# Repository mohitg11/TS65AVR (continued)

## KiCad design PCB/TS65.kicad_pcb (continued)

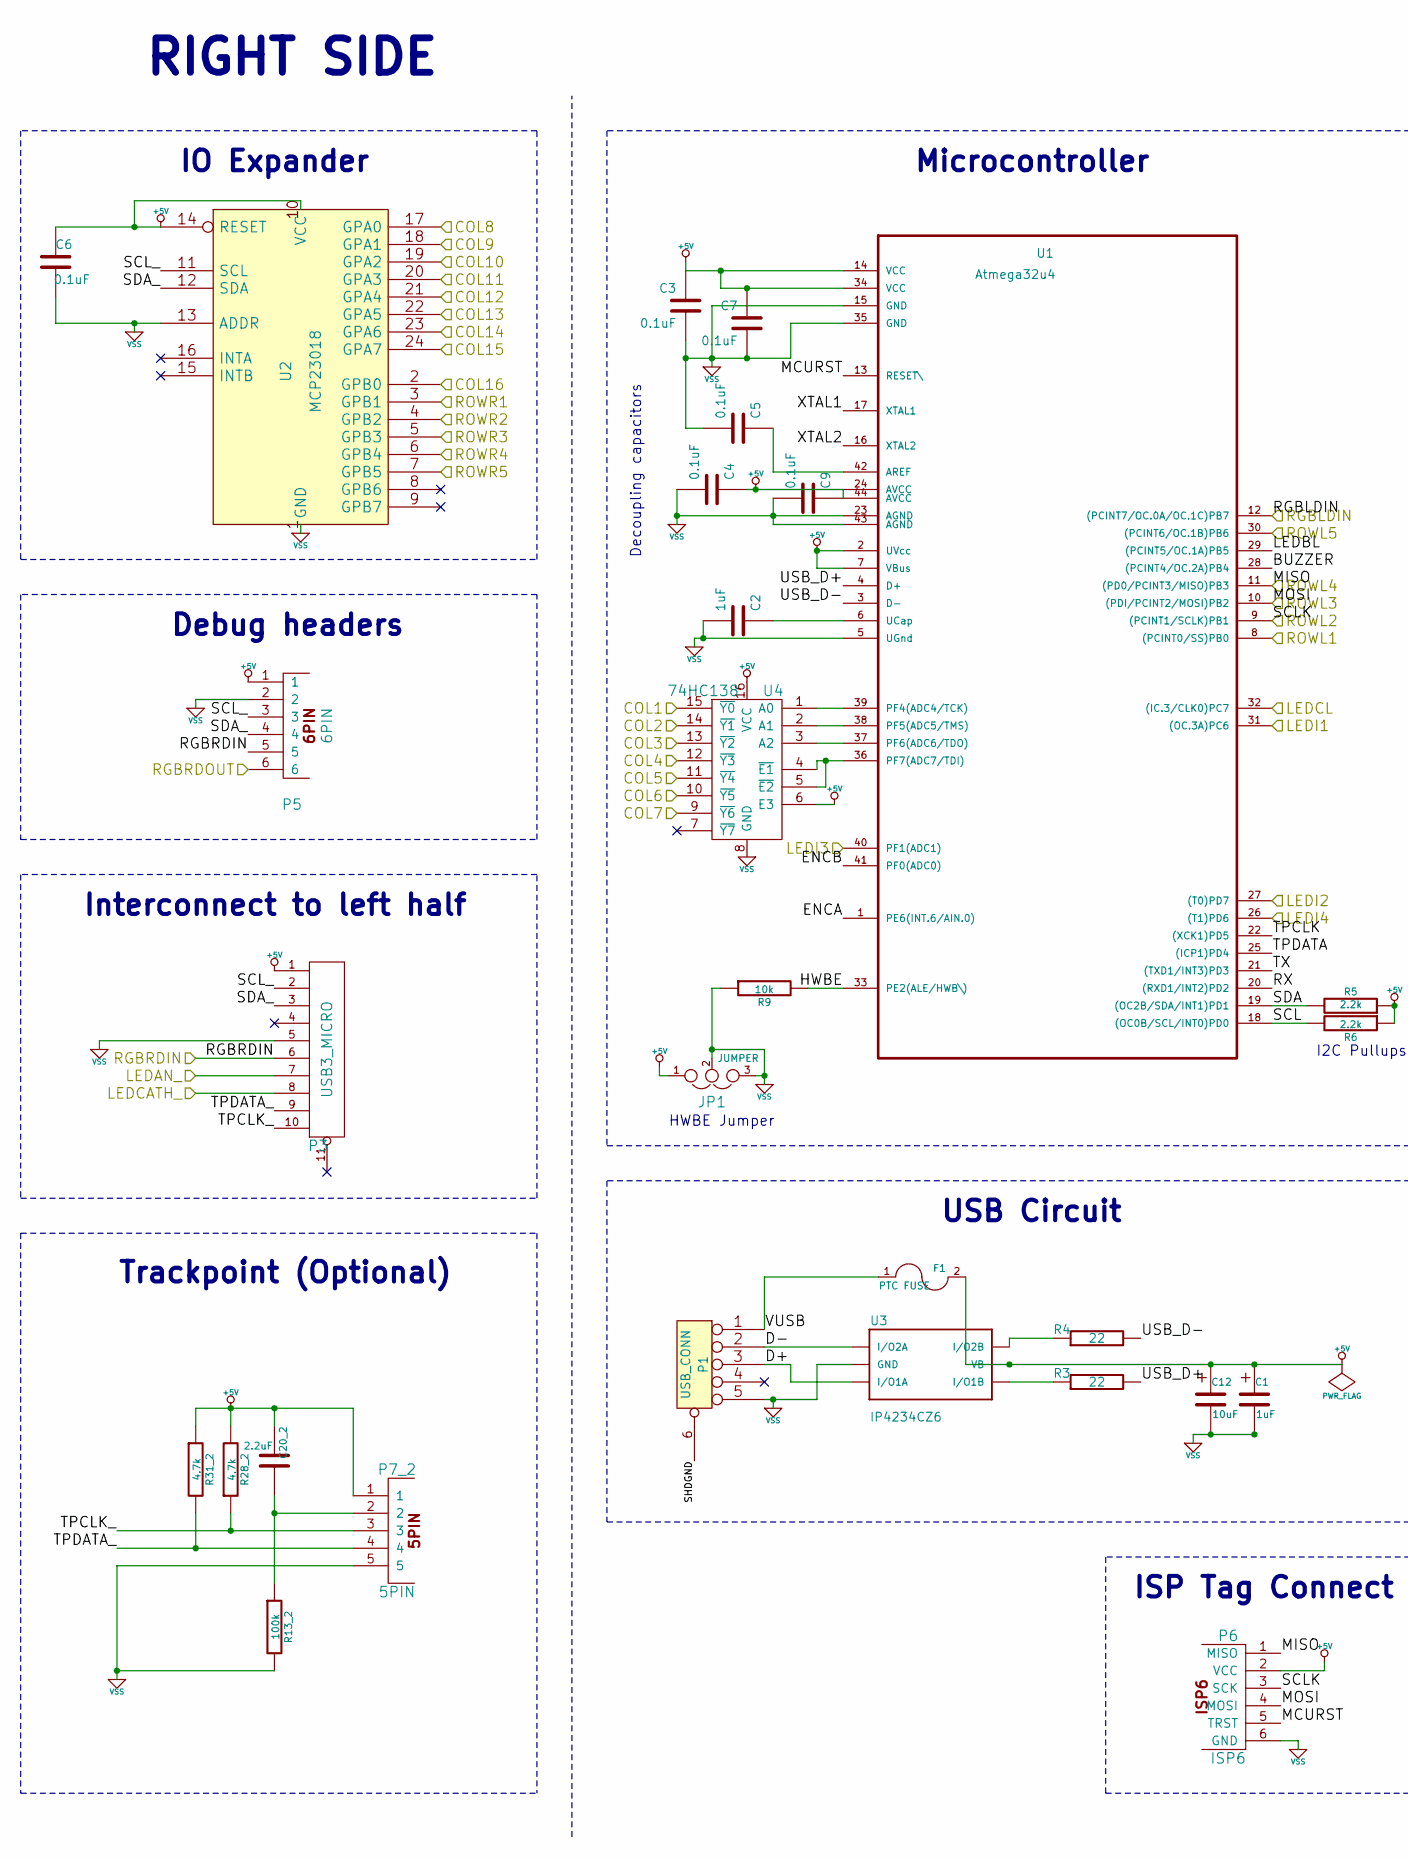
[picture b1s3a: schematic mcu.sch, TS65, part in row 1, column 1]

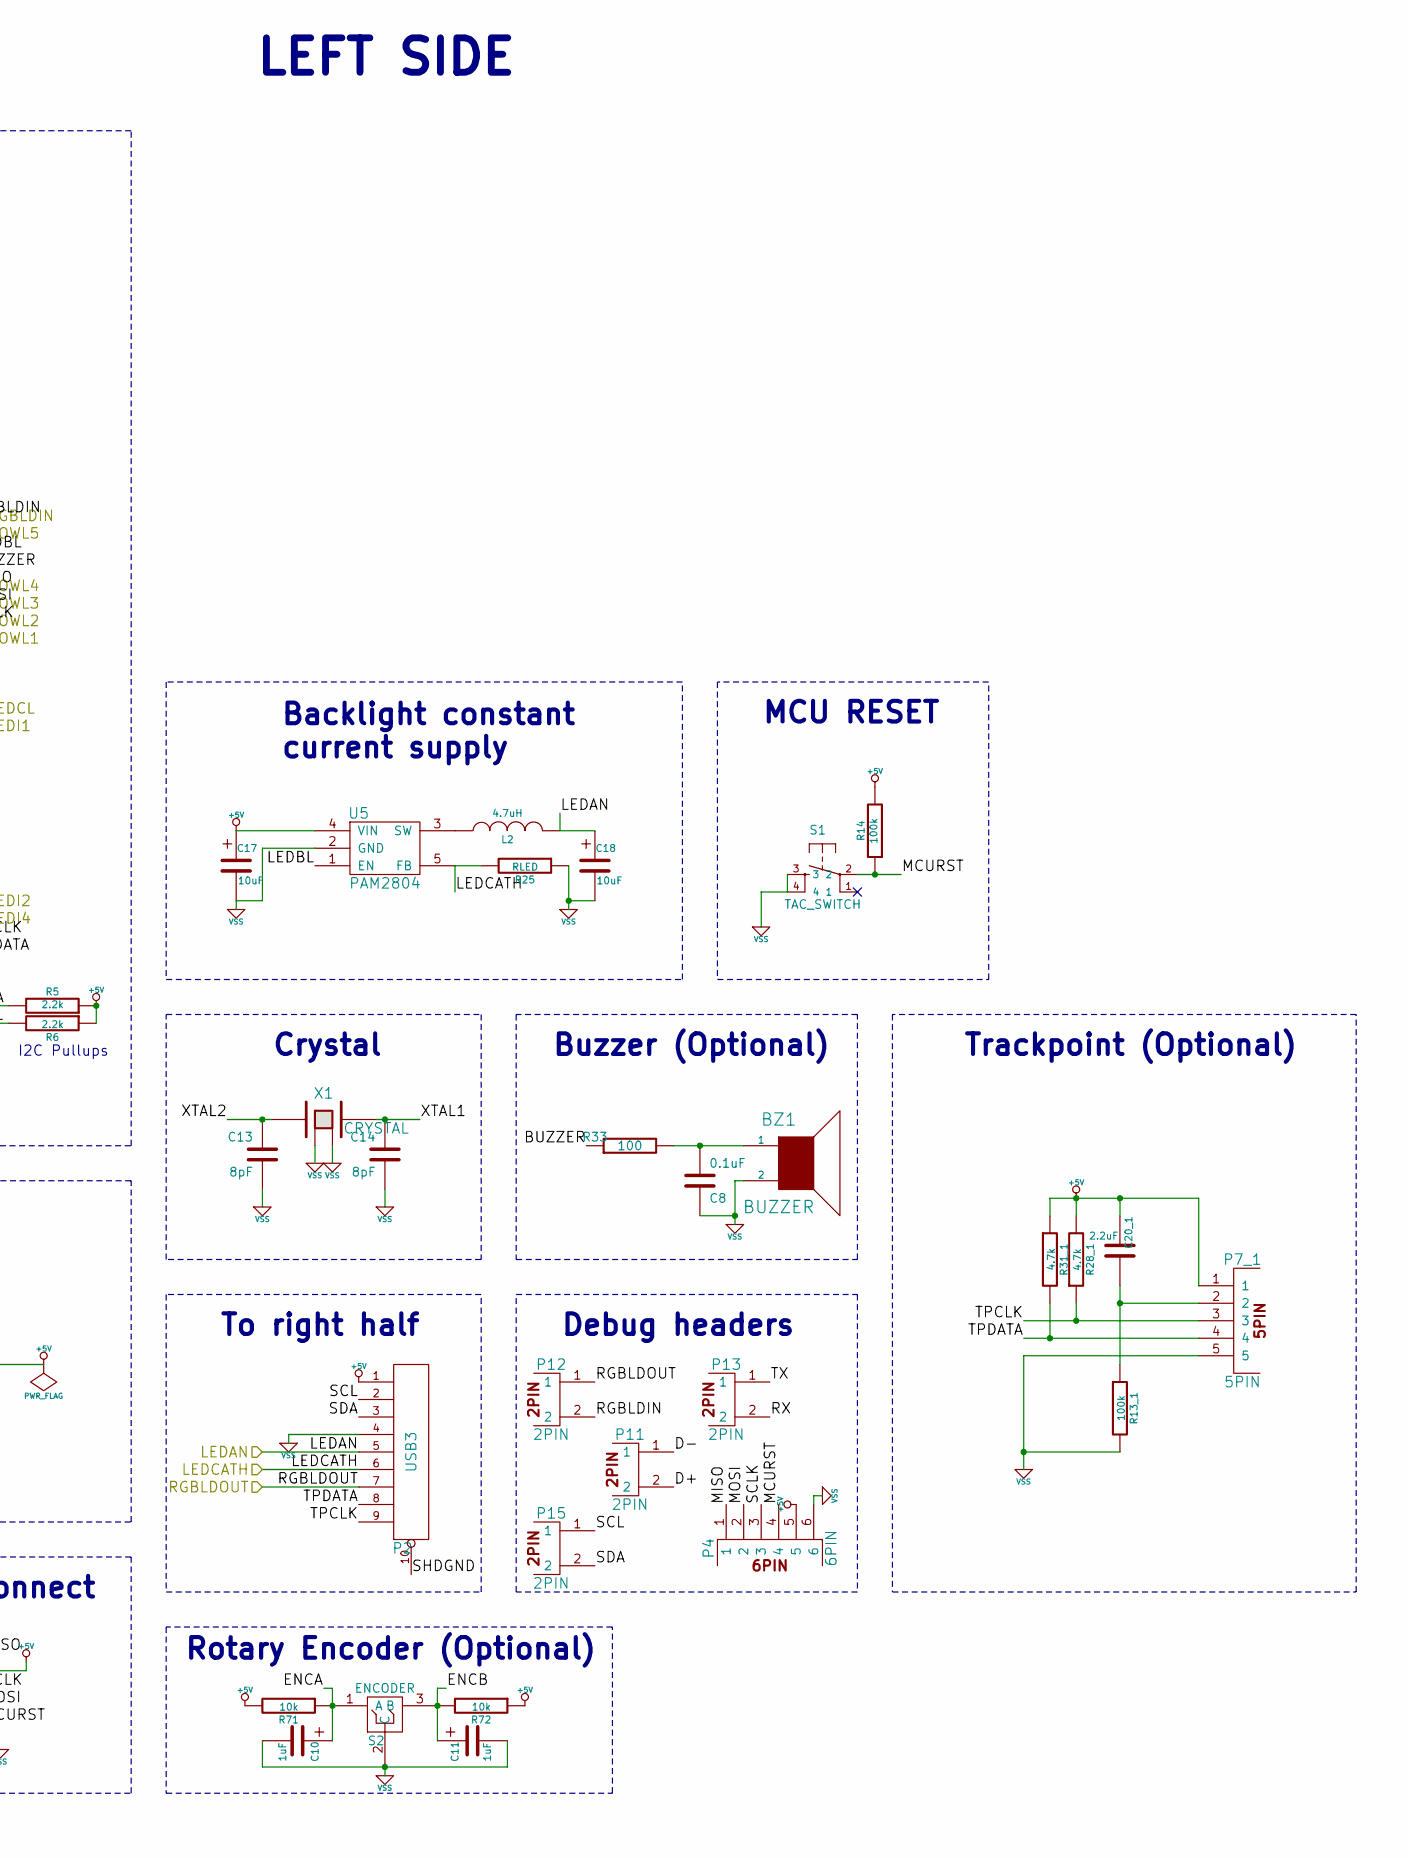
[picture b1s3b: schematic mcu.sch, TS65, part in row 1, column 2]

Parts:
BZ1: BUZZER; BUZZER_SMT
C1, C2, C10, C11: 1uF; SMD_0805
C3, C4, C5, C6, C7, C8, C9: 0.1uF; SMD_0805
C12, C17, C18: 10uF; SMD_0805
C13, C14: 8pF; SMD_0805
C20_1, C20_2: 2.2uF; SMD_0805
F1: PTC FUSE; Fuse_SMD1206
JP1: JUMPER; JUMPER_SMD_3
L2: 4.7uH; Inductor_Bourn_4mmx4mm
P1: USB_CONN; USB_Micro-B
P2: USB3; USB3_AFEMALE_MOD
P3: USB3_MICRO; USB3_MICROB
P4, P5: 6PIN; Pin_Header_1x06
P6: ISP6; TC2030_BIG
P7_1, P7_2: 5PIN; Pin_Header_1x05
P11, P12, P13, P15: 2PIN; Pin_Header_1x02
R3, R4: 22; SMD_0805
R5, R6: 2.2k; SMD_0805
R9, R71, R72: 10k; SMD_0805
R13_1, R13_2, R14: 100k; SMD_0805
R25: RLED; SMD_0805
R28_1, R28_2, R31_1, R31_2: 4.7k; SMD_0805
R33: 100; SMD_0805
S1: TAC_SWITCH; TACT_5.2x5.2
S2: ENCODER; ENCODER_12MM
U1: Atmega32u4; TQFP44
U2: MCP23018; SSOP-24
U3: IP4234CZ6; SOT457
U4: 74HC138; SO-16-N
U5: PAM2804; SOT-23-5
X1: CRYSTAL; NX3225SA

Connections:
+5V: C1.1, C3.1, C4.1, C6.1, C7.1, C9.1, C12.1, C17.1, C20_1.2, C20_2.2, F1.2, JP1.1, P2.1, P3.1, P4.5, P5.1, P6.2 (VCC), P7_1.1, P7_2.1, R5.1, R6.1, R14.2, R28_1.2, R28_2.2, R31_1.1, R31_2.1, R71.2, R72.1, U1.2 (UVcc), U1.7 (VBus), U1.14 (VCC), U1.24 (AVCC), U1.34 (VCC), U1.44 (AVCC), U2.10 (VCC), U2.14 (RESET), U3.5 (VB), U4.6 (E3), U4.16 (VCC), U5.4 (VIN); also elsewhere on the board
/Col1: U4.15 (~Y0); also elsewhere on the board
/Col2: U4.14 (~Y1); also elsewhere on the board
/Col3: U4.13 (~Y2); also elsewhere on the board
/Col4: U4.12 (~Y3); also elsewhere on the board
/Col5: U4.11 (~Y4); also elsewhere on the board
/Col6: U4.10 (~Y5); also elsewhere on the board
/Col7: U4.9 (~Y6); also elsewhere on the board
/Col8: U2.17 (GPA0); also elsewhere on the board
/Col9: U2.18 (GPA1); also elsewhere on the board
/Col10: U2.19 (GPA2); also elsewhere on the board
/Col11: U2.20 (GPA3); also elsewhere on the board
/Col12: U2.21 (GPA4); also elsewhere on the board
/Col13: U2.22 (GPA5); also elsewhere on the board
/Col14: U2.23 (GPA6); also elsewhere on the board
/Col15: U2.24 (GPA7); also elsewhere on the board
/Col16: U2.2 (GPB0); also elsewhere on the board
/RowL1: U1.8 ((PCINT0/SS)PB0); also elsewhere on the board
/RowL2: P4.3, P6.3 (SCK), U1.9 ((PCINT1/SCLK)PB1); also elsewhere on the board
/RowL3: P4.2, P6.4 (MOSI), U1.10 ((PDI/PCINT2/MOSI)PB2); also elsewhere on the board
/RowL4: P4.1, P6.1 (MISO), U1.11 ((PD0/PCINT3/MISO)PB3); also elsewhere on the board
/RowL5: U1.30 ((PCINT6/OC.1B)PB6); also elsewhere on the board
/RowR1: U2.3 (GPB1); also elsewhere on the board
/RowR2: U2.4 (GPB2); also elsewhere on the board
/RowR3: U2.5 (GPB3); also elsewhere on the board
/RowR4: U2.6 (GPB4); also elsewhere on the board
/RowR5: U2.7 (GPB5); also elsewhere on the board
/ledmatrix/LEDAN_: P3.7; also elsewhere on the board
/ledmatrix/LEDCATH_: P3.8; also elsewhere on the board
/ledmatrix/LEDCL: U1.32 ((IC.3/CLK0)PC7); also elsewhere on the board
/ledmatrix/LEDI1: U1.31 ((OC.3A)PC6); also elsewhere on the board
/ledmatrix/LEDI2: U1.27 ((T0)PD7); also elsewhere on the board
/ledmatrix/LEDI3: U1.40 (PF1(ADC1)); also elsewhere on the board
/ledmatrix/LEDI4: U1.26 ((T1)PD6); also elsewhere on the board
/ledmatrix/RGBLDIN: P12.2, U1.12 ((PCINT7/OC.0A/OC.1C)PB7); also elsewhere on the board
/ledmatrix/RGBRDIN: P3.6, P5.5; also elsewhere on the board
/ledmatrix/RGBRDOUT: P5.6; also elsewhere on the board
/mcu/BUZZER: R33.1, U1.28 ((PCINT4/OC.2A)PB4)
/mcu/D+: P1.3, P11.2, U3.4 (I/O1A)
/mcu/D-: P1.2, P11.1, U3.3 (I/O2A)
/mcu/ENCA: C10.1, R71.1, S2.1 (A), U1.1 (PE6(INT.6/AIN.0))
/mcu/ENCB: C11.1, R72.2, S2.3 (B), U1.41 (PF0(ADC0))
/mcu/HWBE: R9.2, U1.33 (PE2(ALE/HWB\))
/mcu/LEDBL: U1.29 ((PCINT5/OC.1A)PB5), U5.1 (EN)
/mcu/MCURST: P4.4, P6.5 (TRST), R14.1, S1.2, U1.13 (RESET\)
/mcu/RX: P13.2, U1.20 ((RXD1/INT2)PD2)
/mcu/SCL: P2.2, P15.1, R6.2, U1.18 ((OC0B/SCL/INT0)PD0)
/mcu/SCL_: P3.2, P5.3, U2.11 (SCL)
/mcu/SDA: P2.3, P15.2, R5.2, U1.19 ((OC2B/SDA/INT1)PD1)
/mcu/SDA_: P3.3, P5.4, U2.12 (SDA)
/mcu/SHDGND: P1.6, P2.10
/mcu/TPCLK: P2.9, P7_1.3, R28_1.1, U1.22 ((XCK1)PD5)
/mcu/TPCLK_: P3.10, P7_2.3, R28_2.1
/mcu/TPDATA: P2.8, P7_1.4, R31_1.2, U1.25 ((ICP1)PD4)
/mcu/TPDATA_: P3.9, P7_2.4, R31_2.2
/mcu/TX: P13.1, U1.21 ((TXD1/INT3)PD3)
/mcu/USB_D+: R3.2, U1.4 (D+)
/mcu/USB_D-: R4.2, U1.3 (D-)
/mcu/VUSB: F1.1, P1.1
/mcu/XTAL1: C14.1, U1.17 (XTAL1), X1.3
/mcu/XTAL2: C13.1, U1.16 (XTAL2), X1.1
unnamed: BZ1.1, C8.2, R33.2
unnamed: C2.1, U1.6 (UCap)
unnamed: C5.1, U1.42 (AREF)
unnamed: C20_1.1, P7_1.2, R13_1.1
unnamed: C20_2.1, P7_2.2, R13_2.1
unnamed: L2.1, U5.3 (SW)
unnamed: R3.1, U3.6 (I/O1B)
unnamed: R4.1, U3.1 (I/O2B)
unnamed: U1.36 (PF7(ADC7/TDI)), U4.4 (~E1), U4.5 (~E2)
unnamed: U1.37 (PF6(ADC6/TDO)), U4.3 (A2)
unnamed: U1.38 (PF5(ADC5/TMS)), U4.2 (A1)
unnamed: U1.39 (PF4(ADC4/TCK)), U4.1 (A0)
VSS: BZ1.2, C1.2, C2.2, C3.2, C4.2, C5.2, C6.2, C7.2, C8.1, C9.2, C10.2, C11.2, C12.2, C13.2, C14.2, C17.2, C18.2, JP1.2, JP1.3, P1.5, P2.4, P3.5, P4.6, P5.2, P6.6 (GND), P7_1.5, P7_2.5, R9.1, R13_1.2, R13_2.2, R25.1, S1.3, S1.4, S2.2 (C), U1.5 (UGnd), U1.15 (GND), U1.23 (AGND), U1.35 (GND), U1.43 (AGND), U2.1 (GND), U2.13 (ADDR), U3.2 (GND), U4.8 (GND), U5.2 (GND), X1.2, X1.4; also elsewhere on the board

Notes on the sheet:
IO Expander
Interconnect to left half
Debug headers
Trackpoint (Optional)
RIGHT SIDE
USB Circuit
To right half
Backlight constant current supply
ISP Tag Connect
Crystal
MCU RESET
Buzzer (Optional)
Microcontroller
HWBE Jumper
I2C Pullups
Decoupling capacitors
LEFT SIDE
Rotary Encoder (Optional)

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
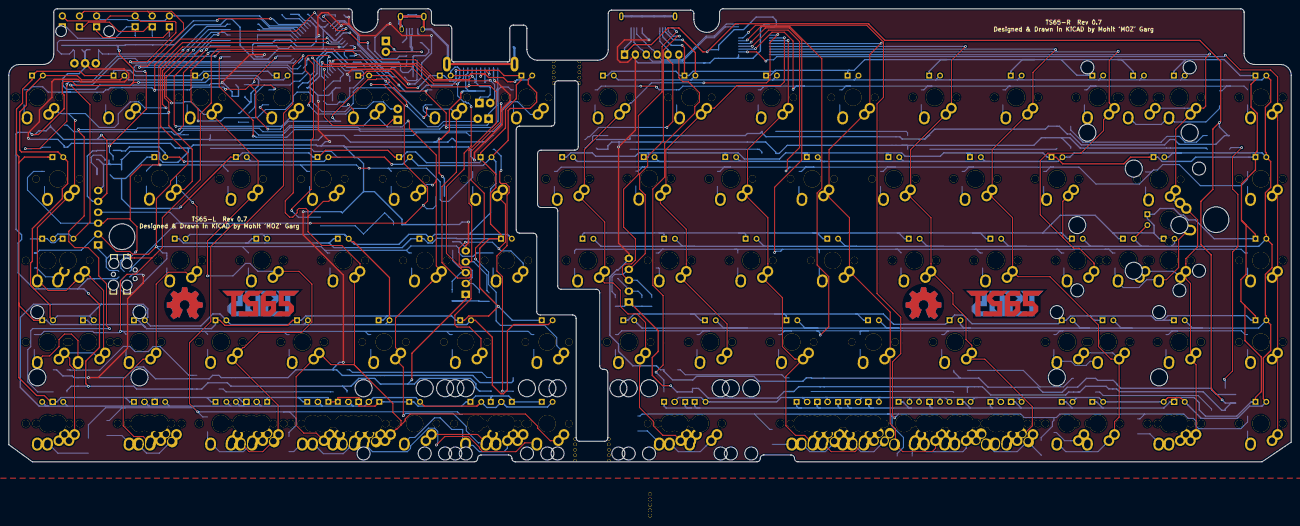
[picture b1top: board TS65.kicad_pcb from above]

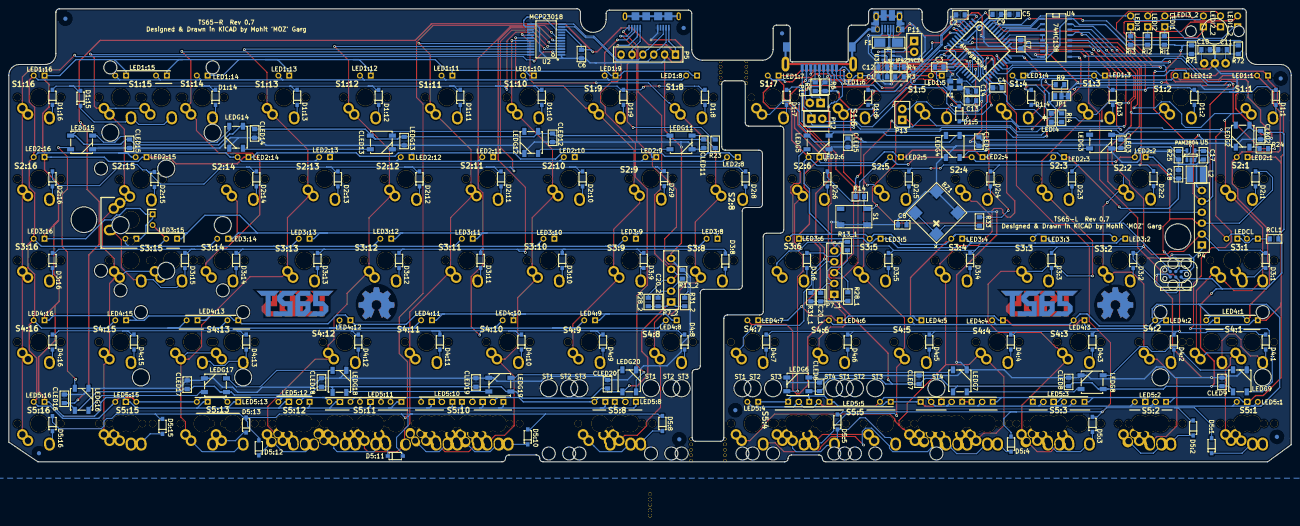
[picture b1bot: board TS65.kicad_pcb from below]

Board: 2 copper layers, 299.5 x 105.8 mm, 437 parts (193 on the bottom side), 173 nets.

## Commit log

2016-05-02 Rev 0.6
2016-05-10 Upload BOM
2016-05-20 Rev 0.7
2017-04-27 Update BOM
    Added designators for WS2812B
2017-05-19 Rev 0.7.1
    - Replace P2 with in stock part
    - Update quantity for P2, P3
2017-05-19 0.7.1
    - Corrected pin mappings for right half connector
2017-05-19 Rev 0.7.1
    - Corrected pin mappings for right half connector
2017-05-19 Rev 0.7.1
    - Replace P2 with in stock part
    - Update quantity for P2,P3
2017-07-20 Add 3d printed case for the TS65 keyboard
    Reference https://geekhack.org/index.php?topic=79161.msg2462175#msg2462175
2017-07-20 Remove unneeded hole from bottom left
    Remove unneeded hole from bottom left
2017-07-22 Increase gap between keys and case
2017-07-24 Rename Case/TS65.svg to Case/Layered/TS65.svg
2018-07-23 Adding re-modeled Fusion360 case model.
2018-07-31 Swapping individual options for single 'flexible' layout. Adding trackpoint models.
